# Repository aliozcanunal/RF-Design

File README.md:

# RF to USB Dongle

**Installation of Kicad on Ubuntu**

```bash
sudo add-apt-repository --yes ppa:kicad/kicad-5.1-releases

sudo apt update

sudo apt install --install-recommends kicad
```

**After installation;**

```bash
cd ~/Desktop

git clone "https://github.com/aliozcanunal/RF-Design"

cd /RF-Design/Rf -Design

kicad Rf -Design.pro
```

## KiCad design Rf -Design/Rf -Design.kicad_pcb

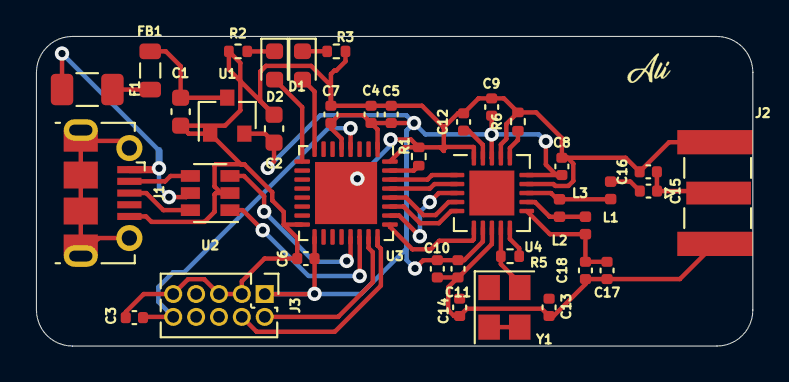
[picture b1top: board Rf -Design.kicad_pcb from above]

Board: 4 copper layers, 39.8 x 17.2 mm, 38 parts (0 on the bottom side), 33 nets.

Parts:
C1, C2: 10u; C_0603_1608Metric
C3, C5, C6, C7: 100n; C_0402_1005Metric
C4: 1u; C_0402_1005Metric
C8: 10u; C_0402_1005Metric
C9, C10, C11: 10n; C_0402_1005Metric
C12: 33n; C_0402_1005Metric
C13, C14: 12p; C_0402_1005Metric
C15: 1p5; C_0402_1005Metric
C16: 1p; C_0402_1005Metric
C17: 2n2; C_0402_1005Metric
C18: 4p7; C_0402_1005Metric
D1, D2: LED; LED_0603_1608Metric
F1: 100mA; Fuse_1206_3216Metric
FB1: 100 @ 100MHz; L_0805_2012Metric
J1: USB_B_Micro; USB_Micro-B_Molex-105017-0001
J2: SMA; SMA_Samtec_SMA-J-P-X-ST-EM1_EdgeMount
J3: SWD; PinHeader_2x05_P1.27mm_Vertical
L1, L2, L3: 3n9; L_0402_1005Metric
R1, R6: 10K; R_0402_1005Metric
R2, R3: 2.2K; R_0402_1005Metric
R5: 1M; R_0402_1005Metric
U1: XC6206PxxxMR; SOT-23
U2: USBLC6-2SC6; SOT-23-6
U3: STM32L432KBUx; QFN-32-1EP_5x5mm_P0.5mm_EP3.45x3.45mm
U4: nRF24L01P; QFN-20-1EP_4x4mm_P0.5mm_EP2.5x2.5mm
Y1: Crystal_GND23; Crystal_SMD_3225-4Pin_3.2x2.5mm

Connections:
+3V3: C2.1, C4.1, C5.1, C6.1, C7.1, C8.1, C9.1, C10.1, C11.1, J3.1, U1.2, U3.1, U3.5, U3.17, U4.7, U4.15, U4.18
+5V: F1.2, J1.1, U2.5
GND: C1.2, C2.2, C3.2, C4.2, C5.2, C6.2, C7.2, C8.2, C9.2, C10.2, C11.2, C12.2, C13.2, C14.2, C16.2, C17.2, C18.2, J1.5, J2.2, J3.3, J3.5, J3.9, R1.2, R2.2, R3.2, R6.2, U1.1, U2.2, U3.16, U3.32, U3.33, U4.8, U4.14, U4.17, U4.20
NRF_ANT1: L2.2, L3.2, U4.12
NRF_ANT2: L1.1, L2.1, U4.13
NRF_CE: U3.30, U4.1
NRF_IRQ: U3.25, U4.6
NRF_VDD_PA: C17.1, C18.1, L3.1, U4.11
NRF_XC1: C13.1, R5.2, U4.10, Y1.1
NRF_XC2: C14.1, R5.1, U4.9, Y1.4
NRST: C3.1, J3.10, U3.4
unnamed: C1.1, FB1.1, U1.3
unnamed: C12.1, U4.19
unnamed: C15.1, L1.2
unnamed: C15.2, C16.1, J2.1
unnamed: D1.1, R2.1
unnamed: D1.2, U3.9
unnamed: D2.1, R3.1
unnamed: D2.2, U3.8
unnamed: F1.1, FB1.2
unnamed: R1.1, U3.31
unnamed: R6.1, U4.16
unnamed: Y1.2, Y1.3
SPI3_!CS: U3.29, U4.2
SPI3_MISO: U3.27, U4.5
SPI3_MOSI: U3.28, U4.4
SPI3_SCK: U3.26, U4.3
SWCLK: J3.4, U3.24
SWDIO: J3.2, U3.23
USB_CONN_D+: J1.3, U2.6
USB_CONN_D-: J1.2, U2.4
USB_D+: U2.1, U3.22
USB_D-: U2.3, U3.21

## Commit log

2021-02-27 Route tracks are arranged
2021-02-27 Rf - Design.png
2021-02-27 The texts on the f-silk layer are fixed
